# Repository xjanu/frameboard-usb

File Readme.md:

FrameBoard USB
==============

A USB keyboard powered by the Framework Laptop 13 [keyboard matrix](https://frame.work/products/keyboard?v=FRANBKEN05). It was developed as part of the [PV191](https://is.muni.cz/predmet/fi/jaro2024/PV191?lang=en) course at [FI MU](https://www.fi.muni.cz/).

## Board

The board schematic and layout can be found in the `board/` directory. It was designed in [KiCad](https://www.kicad.org/).

## Firmware

The firmware is based on the [QMK firmware](https://docs.qmk.fm/). It can be found in the fork of QMK, here: [FrameBoard QMK fork](https://github.com/xjanu/qmk_firmware/)

TODO: instructions for flashing and building

## Errata

TODO

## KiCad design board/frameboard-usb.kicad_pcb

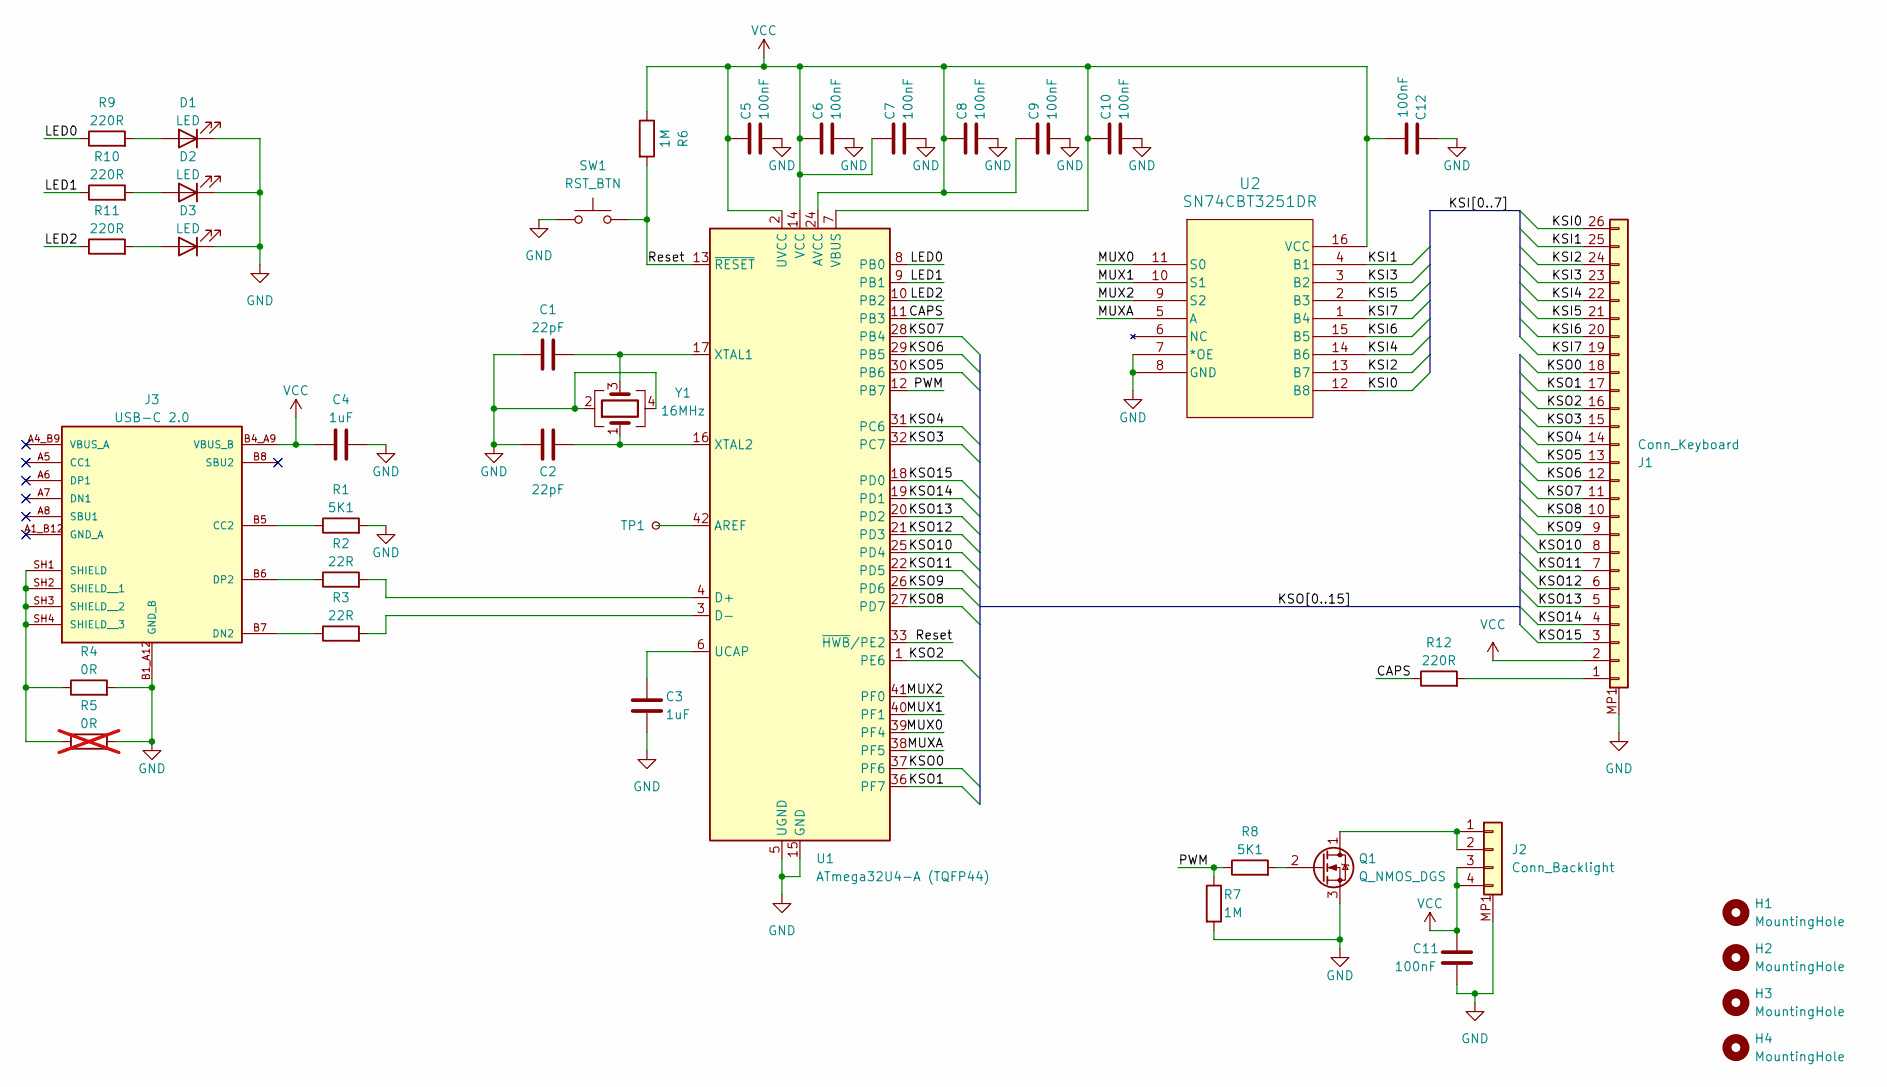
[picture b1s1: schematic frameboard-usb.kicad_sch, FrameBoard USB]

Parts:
C1, C2: 22pF; C_0805_2012Metric; Digikey C0805C220F1HAC7800
C3, C4: 1uF; C_0805_2012Metric; Digikey CL21B105KAFNNNE
C5, C6, C7, C8, C9, C10, C11, C12: 100nF; C_0805_2012Metric; Digikey CL21B104KBCNNNC
D1, D2, D3: LED; LED_0805_2012Metric; Digikey B1701UY--20D000214U1930
H1, H2, H3, H4: MountingHole; MountingHole_2.2mm_M2
J1: Conn_Keyboard; 046809626210846; Digikey 046809626210846+
J2: Conn_Backlight; conn_backlight; Digikey F518-1A7A1-11004
J3: USB-C 2.0; AMPHENOL_GSB1C4621DS1HR; PARTREV AX1; Digikey GSB1C4621DS1HR
Q1: Q_NMOS_DGS; SOT-323_SC-70; Digikey 4878-2N7002WCT-ND
R1, R8: 5K1; R_0805_2012Metric; Digikey RC0805JR-075K1L
R2, R3: 22R; R_0805_2012Metric; Digikey RC0805FR-0722RL
R4: 0R; R_0805_2012Metric; Digikey RC0805JR-070RL
R5: 0R; R_0805_2012Metric; Digikey RC0805JR-070RL; not fitted
R6, R7: 1M; R_0805_2012Metric; Digikey RC0805FR-071ML
R9, R10, R11, R12: 220R; R_0805_2012Metric; Digikey RC0805FR-07220RL
SW1: RST_BTN; button; Digikey PTS636 SP43 LFS
TP1: TestPoint; testpoint
U1: ATmega32U4-A (TQFP44); TQFP-44_10x10mm_P0.8mm; Digikey ATMEGA32U4-AU
U2: SN74CBT3251DR; SOIC-16_ONS; Digikey SN74CBT3251DR
Y1: 16MHz; Crystal_SMD_3225-4Pin_3.2x2.5mm; Digikey RH100-16.000-18-2030-EXT-TR

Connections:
/CAPS: R12.1, U1.11 (PB3)
/KSI0: J1.26, U2.12 (B8)
/KSI1: J1.25, U2.4 (B1)
/KSI2: J1.24, U2.13 (B7)
/KSI3: J1.23, U2.3 (B2)
/KSI4: J1.22, U2.14 (B6)
/KSI5: J1.21, U2.2 (B3)
/KSI6: J1.20, U2.15 (B5)
/KSI7: J1.19, U2.1 (B4)
/KSO0: J1.18, U1.37 (PF6)
/KSO1: J1.17, U1.36 (PF7)
/KSO2: J1.16, U1.1 (PE6)
/KSO3: J1.15, U1.32 (PC7)
/KSO4: J1.14, U1.31 (PC6)
/KSO5: J1.13, U1.30 (PB6)
/KSO6: J1.12, U1.29 (PB5)
/KSO7: J1.11, U1.28 (PB4)
/KSO8: J1.10, U1.27 (PD7)
/KSO9: J1.9, U1.26 (PD6)
/KSO10: J1.8, U1.25 (PD4)
/KSO11: J1.7, U1.22 (PD5)
/KSO12: J1.6, U1.21 (PD3)
/KSO13: J1.5, U1.20 (PD2)
/KSO14: J1.4, U1.19 (PD1)
/KSO15: J1.3, U1.18 (PD0)
/LED0: R9.1, U1.8 (PB0)
/LED1: R10.1, U1.9 (PB1)
/LED2: R11.1, U1.10 (PB2)
/MUX0: U1.39 (PF4), U2.11 (S0)
/MUX1: U1.40 (PF1), U2.10 (S1)
/MUX2: U1.41 (PF0), U2.9 (S2)
/MUXA: U1.38 (PF5), U2.5 (A)
/PWM: R7.1, R8.1, U1.12 (PB7)
/Reset: R6.2, SW1.2, U1.13 (~RESET), U1.33 (~HWB/PE2)
GND: C1.2, C2.2, C3.2, C4.2, C5.2, C6.2, C7.2, C8.2, C9.2, C10.2, C11.2, C12.1, D1.1 (K), D2.1 (K), D3.1 (K), J1.MP1, J1.MP2, J2.MP1, J2.MP2, J3.B1_A12 (GND_B), Q1.3 (S), R1.2, R4.2, R5.2, R7.2, SW1.1, U1.5 (UGND), U1.15 (GND), U1.23 (GND), U1.35 (GND), U1.43 (GND), U2.7 (*OE), U2.8 (GND), Y1.2, Y1.4
unnamed: D1.2 (A), R9.2
unnamed: D2.2 (A), R10.2
unnamed: D3.2 (A), R11.2
unnamed: J1.1, R12.2
unnamed: J2.1, J2.2, Q1.1 (D)
unnamed: J3.B5 (CC2), R1.1
unnamed: J3.B7 (DN2), R3.1
unnamed: J3.B6 (DP2), R2.1
unnamed: J3.SH1 (SHIELD), J3.SH2 (SHIELD__1), J3.SH3 (SHIELD__2), J3.SH4 (SHIELD__3), R4.1, R5.1
unnamed: Q1.2 (G), R8.2
unnamed: TP1.1, U1.42 (AREF)
unnamed: R2.2, U1.4 (D+)
unnamed: R3.2, U1.3 (D-)
unnamed: C3.1, U1.6 (UCAP)
unnamed: C1.1, U1.17 (XTAL1), Y1.3
unnamed: C2.1, U1.16 (XTAL2), Y1.1
VCC: C4.1, C5.1, C6.1, C7.1, C8.1, C9.1, C10.1, C11.1, C12.2, J1.2, J2.3, J2.4, J3.B4_A9 (VBUS_B), R6.1, U1.2 (UVCC), U1.7 (VBUS), U1.14 (VCC), U1.24 (AVCC), U1.34 (VCC), U1.44 (AVCC), U2.16 (VCC)

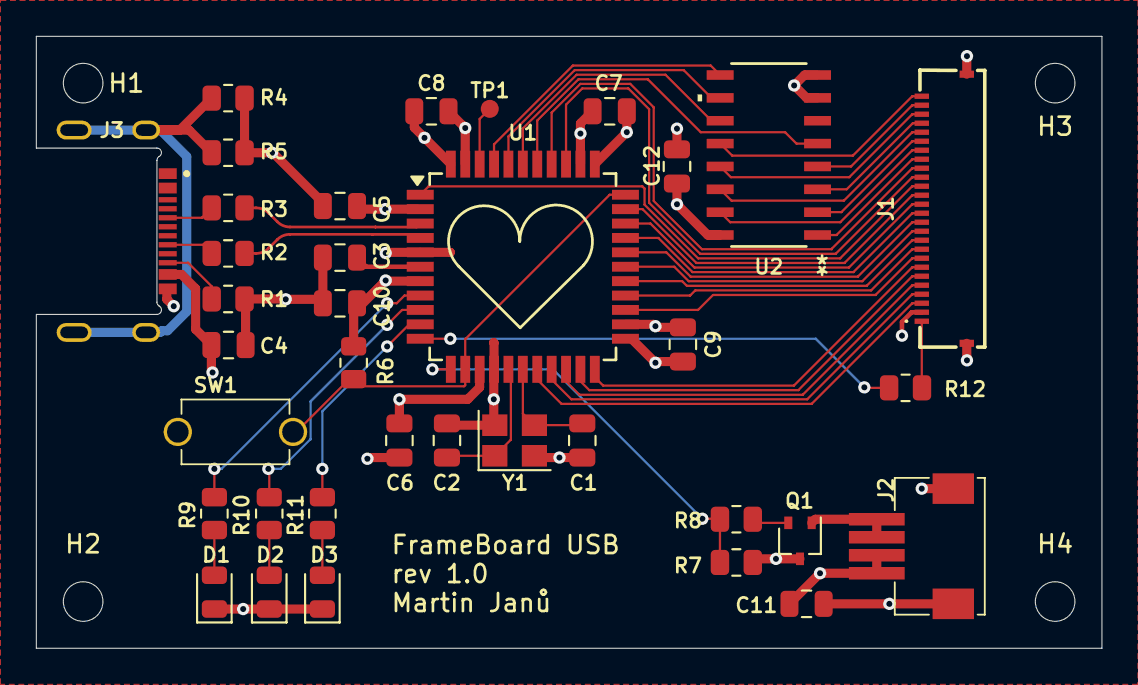
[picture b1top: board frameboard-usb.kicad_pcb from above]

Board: 4 copper layers, 59.2 x 34.0 mm, 40 parts (0 on the bottom side), 52 nets.

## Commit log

2024-06-14 Add board design files
2024-06-14 Add an image
